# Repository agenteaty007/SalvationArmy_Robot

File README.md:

SalvationArmy_Robot
===================

Pasadena Salvation Army PAL Program Robot for Fall 2014

Files:

- EAGLE schematics and board files

- Board DXF

- Schematic PDF

- Gerber board files

- Arduino code for bluetooth control

- BOM for electronic board and motors

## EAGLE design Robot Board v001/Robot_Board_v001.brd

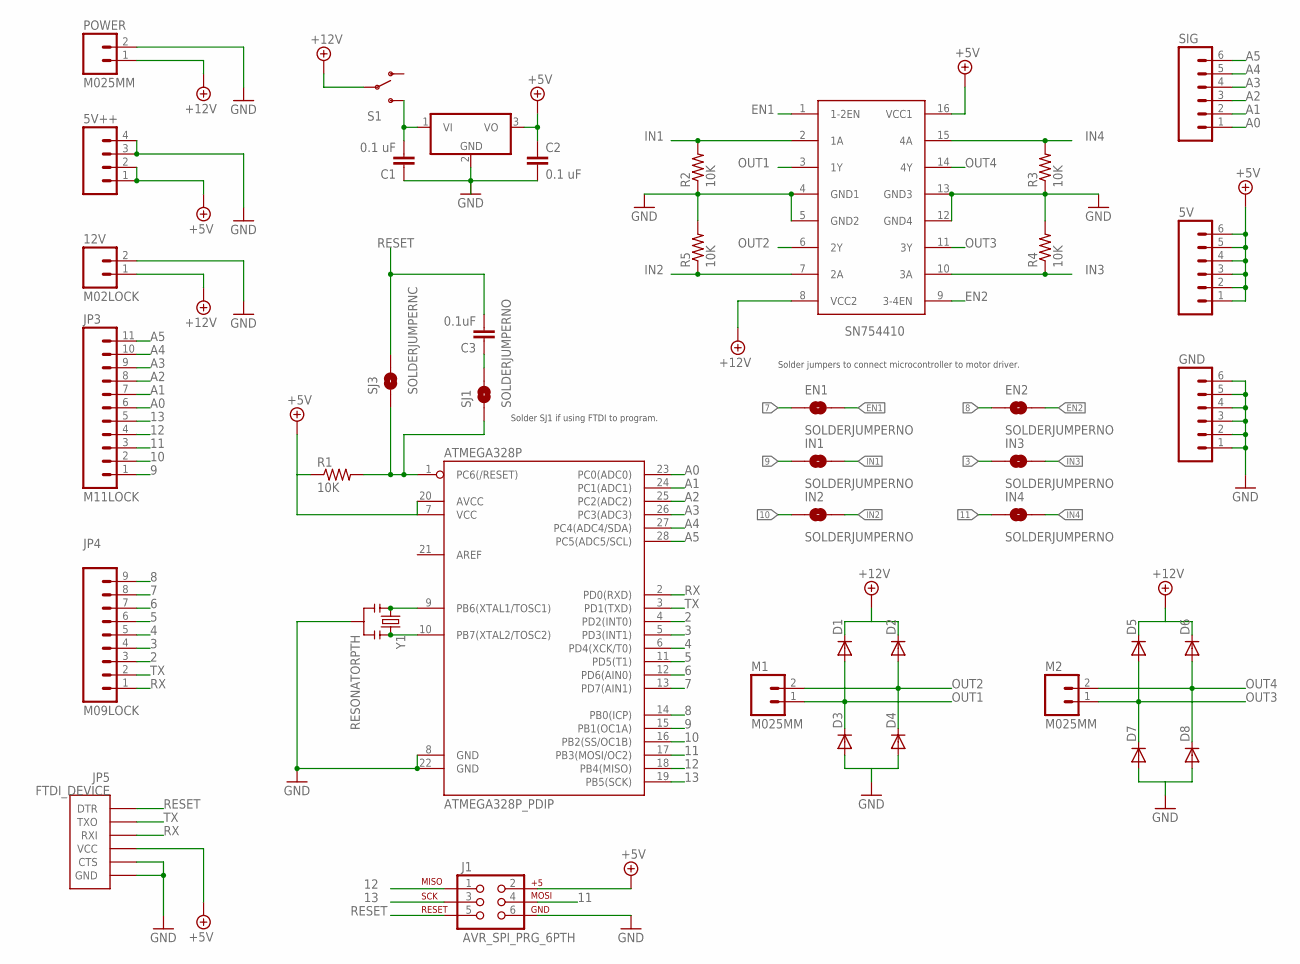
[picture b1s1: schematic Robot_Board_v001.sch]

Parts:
5V: M06SIP; 1X06
5V++: M04LOCK; 1X04_LOCK
12V: M02LOCK; 1X02_LOCK
7805: 7805TV; TO220V
ATMEGA328P: ATMEGA328P_PDIP; DIL28-3
C1, C2: 0.1 uF; CAP-PTH-5MM
C3: 0.1uF; CAP-PTH-5MM
D1, D2, D3, D4, D5, D6, D7, D8: DIODEPTH; DIODE-1N4001
EN1, EN2: SOLDERJUMPERNO; SJ_2S-NO
GND: M06SIP; 1X06
IN1, IN2, IN3, IN4: SOLDERJUMPERNO; SJ_2S-NO
J1: AVR_SPI_PRG_6PTH; 2X3
JP3: M11LOCK; 1X11_LOCK
JP4: M09LOCK; 1X09_LOCK
JP5: FTDI_DEVICE; FTDI_DEVICE_SIDE
M1, M2: M025MM; SCREWTERMINAL-5MM-2
POWER: M025MM; SCREWTERMINAL-5MM-2
R1, R2, R3, R4, R5: 10K; AXIAL-0.4
S1: SWITCH-SPDTPTH; SWITCH-SPDT
SIG: M06SIP; 1X06
SJ1: SOLDERJUMPERNO; SJ_2S-NO
SJ3: SOLDERJUMPERNC; SJ_2S
SN754410: L293D; DIL16
Y1: RESONATORPTH; RESONATOR-PTH

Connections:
2: ATMEGA328P.4 (PD2(INT0)), JP4.3
3: ATMEGA328P.5 (PD3(INT1)), IN3.1, JP4.4
4: ATMEGA328P.6 (PD4(XCK/T0)), JP4.5
5: ATMEGA328P.11 (PD5(T1)), JP4.6
6: ATMEGA328P.12 (PD6(AIN0)), JP4.7
7: ATMEGA328P.13 (PD7(AIN1)), EN1.1, JP4.8
8: ATMEGA328P.14 (PB0(ICP)), EN2.1, JP4.9
9: ATMEGA328P.15 (PB1(OC1A)), IN1.1, JP3.1
10: ATMEGA328P.16 (PB2(SS/OC1B)), IN2.1, JP3.2
11: ATMEGA328P.17 (PB3(MOSI/OC2)), IN4.1, J1.4, JP3.3
12: ATMEGA328P.18 (PB4(MISO)), J1.1, JP3.4
13: ATMEGA328P.19 (PB5(SCK)), J1.3, JP3.5
+5V: 5V.1, 5V.2, 5V.3, 5V.4, 5V.5, 5V.6, 5V++.1, 5V++.2, 7805.3 (VO), ATMEGA328P.7 (VCC), ATMEGA328P.20 (AVCC), C2.1, J1.2, JP5.P$4 (VCC), R1.P$1 (1), SN754410.16 (VCC1)
+12V: 12V.1, D1.C, D2.C, D5.C, D6.C, POWER.1, S1.2, SN754410.8 (VCC2)
A0: ATMEGA328P.23 (PC0(ADC0)), JP3.6, SIG.1
A1: ATMEGA328P.24 (PC1(ADC1)), JP3.7, SIG.2
A2: ATMEGA328P.25 (PC2(ADC2)), JP3.8, SIG.3
A3: ATMEGA328P.26 (PC3(ADC3)), JP3.9, SIG.4
A4: ATMEGA328P.27 (PC4(ADC4/SDA)), JP3.10, SIG.5
A5: ATMEGA328P.28 (PC5(ADC5/SCL)), JP3.11, SIG.6
EN1: EN1.2, SN754410.1 (1-2EN)
EN2: EN2.2, SN754410.9 (3-4EN)
GND: 5V++.3, 5V++.4, 12V.2, 7805.2 (GND), ATMEGA328P.8 (GND), ATMEGA328P.22 (GND), C1.1, C2.2, D3.A, D4.A, D7.A, D8.A, GND.1, GND.2, GND.3, GND.4, GND.5, GND.6, J1.6, JP5.P$5 (CTS), JP5.P$6 (GND), POWER.2, R2.P$1 (1), R3.P$1 (1), R4.P$2 (2), R5.P$2 (2), SN754410.4 (GND1), SN754410.5 (GND2), SN754410.12 (GND4), SN754410.13 (GND3), Y1.2
IN1: IN1.2, R2.P$2 (2), SN754410.2 (1A)
IN2: IN2.2, R5.P$1 (1), SN754410.7 (2A)
IN3: IN3.2, R4.P$1 (1), SN754410.10 (3A)
IN4: IN4.2, R3.P$2 (2), SN754410.15 (4A)
unnamed: ATMEGA328P.9 (PB6(XTAL1/TOSC1)), Y1.1
unnamed: ATMEGA328P.10 (PB7(XTAL2/TOSC2)), Y1.3
unnamed: ATMEGA328P.1 (PC6(/RESET)), R1.P$2 (2), SJ1.1, SJ3.1
unnamed: C3.1, SJ1.2
unnamed: 7805.1 (VI), C1.2, S1.3 (S)
OUT1: D1.A, D3.C, M1.1, SN754410.3 (1Y)
OUT2: D2.A, D4.C, M1.2, SN754410.6 (2Y)
OUT3: D5.A, D7.C, M2.1, SN754410.11 (3Y)
OUT4: D6.A, D8.C, M2.2, SN754410.14 (4Y)
RESET: C3.2, J1.5, JP5.P$1 (DTR), SJ3.2
RX: ATMEGA328P.2 (PD0(RXD)), JP4.1, JP5.P$3 (RXI)
TX: ATMEGA328P.3 (PD1(TXD)), JP4.2, JP5.P$2 (TXO)

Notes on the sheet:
Solder SJ1 if using FTDI to program.
Solder jumpers to connect microcontroller to motor driver.

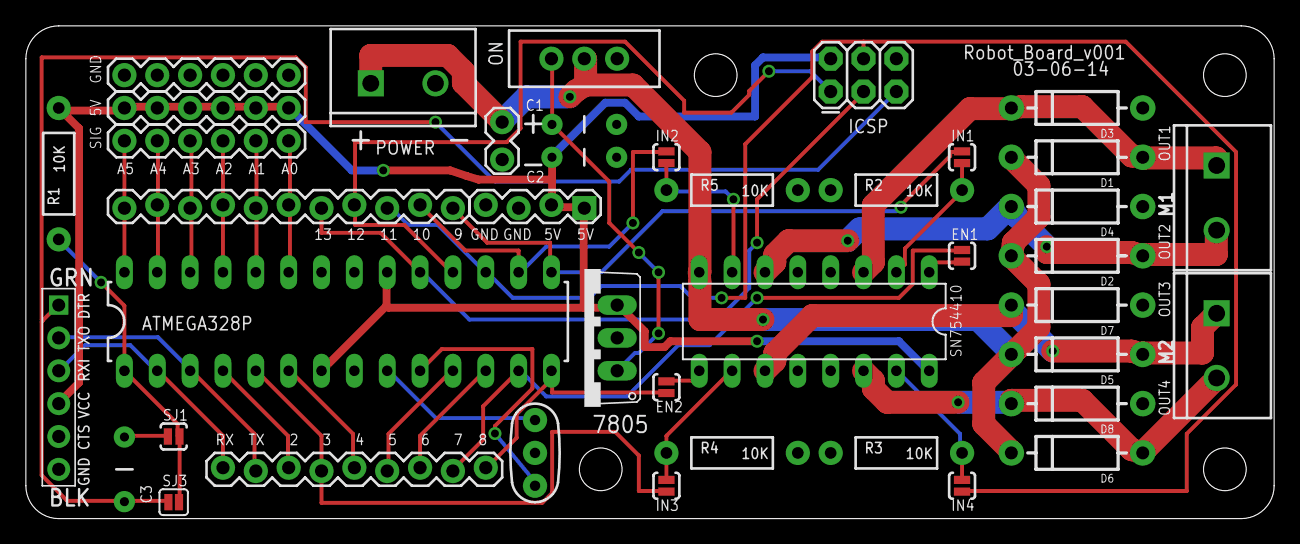
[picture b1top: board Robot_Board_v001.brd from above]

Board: 2 copper layers, 96.5 x 38.1 mm, 45 parts (0 on the bottom side), 39 nets.

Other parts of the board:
U$1, U$2, U$3, U$4: STAND-OFF

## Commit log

2014-08-31 First Commit with basic files
    EAGLE schematics and board files
    Schematic PDF
    Gerber board files
    Arduino code for bluetooth control
    BOM for electronic board and motors
2014-09-02 Editing BOM
2014-09-02 updating BOM
2014-09-02 update BOM
2014-09-02 removing zip file of gerber files
2014-09-05 Fix DXF, add BOM PDF and board labels image.
    DXF used to show traces, not anymore.
    An image file has been added for reference when populating the board.
    BOM PDF only contains the parts required to populate the board and make
    a basic robot. Good to be used as a check list.
2015-02-04 Arduino Code and Robot Board v001 files
    Demo code for Robot Board using Bluetooth module
    Robot Board v001 eagle files and PDF
2015-02-04 Robot Board v001 img

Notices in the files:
parts and their libraries:
SparkFun-DigitalIC: Licensing: CC v3.0 Share-Alike You are welcome to use this library for commercial purposes.
